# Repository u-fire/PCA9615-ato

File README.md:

# PCA9615

📒 [Datasheet](https://www.nxp.com/docs/en/data-sheet/PCA9615.pdf)

This repository is an [atopile](https://atopile.io/) module for the PCA9615, 2-channel multipoint Fast-mode differential I2C-bus. In other words, it lets
you use I2C like you might use MODBUS, ie. over long wires and through noisy environments. 

## 🏁 Get started
### Installation
From inside a project directory terminal: `ato install PCA9615-ato`

### Code
```ato
from "pca9615/elec/src/pca9615.ato" import PCA9615
from "generics/interfaces.ato" import DiffPair, Power, I2C, GPIO

module Test:
    # define virtual buses, connect these to physical components/pins
    power = new Power
    d_sda = new DiffPair
    d_scl = new DiffPair
    i2c = new I2C
    power_a_2v3_5v5 = new Power
    power_b_3v0_5v5 = new Power
    differential_side_power = new Power
    en = new GPIO

    # define the PCA9615
    pca9615 = new PCA9615

    # PCA9615 enable pin is driven high be an internal pullup
    # to disable chip, drive low
    en ~ pca9615.en

    # connect power to normal I2C side
    power_a_2v3_5v5 ~ pca9615.power_a_2v3_5v5

    # differential power can be seperate or the same as the I2C side
    pca9615.power_b_3v0_5v5 ~ power_a_2v3_5v5
    # - or -
    pca9615.power_b_3v0_5v5 ~ differential_side_power

    # normal I2C connection
    i2c ~ pca9615.i2c

    # differential pairs
    d_sda ~ pca9615.d_sda
    d_scl ~ pca9615.d_scl
```

## 🤔 Design Considerations
- d_sda and d_scl must be routed as differential pairs (`6` in KiCAD PCB Editor)
- power on the I2C side can be separate from the differential side, common grounds are not required
- the I2C side can accept between 2.3 - 5.5 volts
- the differential side can accept 3.0 - 5.5 volts
- an RJ45 connector and CAT6 cable work well for making the connections

## 🔌 Connections

|MCU        |       | MCU PCA9615   |       |Sensor PCA9615     | | Sensor |
|-------:   |-:    |---:                  |:-:         |:---           |:-: | :-|
|  |      | MCU PCA9615.d_SDA 🟩|~            |🟩 PCA9615.d_SDA|~ | 
| |      | MCU PCA9615.d_SCL 🟪|~            |🟪 PCA9615.d_SCL|~
| MCU.SDA 🟨 |~      | 🟨 PCA9615.SDA 🟨|            |🟨 PCA9615.SDA|~ |🟨 Sensor.SDA
| MCU.SCL 🟦 |~      | 🟦 PCA9615.SCL 🟦|            |🟦 PCA9615.SCL|~ |🟦 Sensor.SCL
| *MCU.VCC* 🟥      | ~| 🟥 *PCA9615.VCC* 🟥 |*(optional)*|🟥 *PCA9615.VCC*|~ | 🟥 *Sensor.VCC*
|**MCU.GND**⬛      |~       | ⬛ **PCA9615.GND** ⬛|*(optional)*|⬛ **PCA9615.GND**|~|⬛ **Sensor.GND**

## ⚡ Programming
Once connected, the sensor (or just the other side) appear as a normal I2C device to the host. Nothing special needs to be done.

## 🙏 Contributing
This design is intended to be a community best-effort at a minimal circuit combining:
- datasheet reference design
- readily available components
- modular and reusable layout

You are greatly encouraged to contribute or discuss any improvements here so that everyone may benefit. 

## License
[CERN-OHL-P v2](https:/cern.ch/cern-ohl)

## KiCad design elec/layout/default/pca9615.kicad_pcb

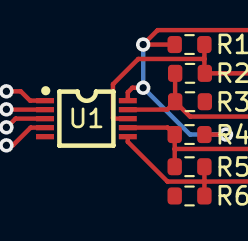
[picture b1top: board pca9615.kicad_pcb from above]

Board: 2 copper layers, 7 parts (0 on the bottom side), 6 nets.

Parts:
R1, R3, R4, R6: Chip Resistor - Surface Mount 300Ohms ±5% 1/10W 0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; R0603
R2, R5: Chip Resistor - Surface Mount 100Ohms ±5% 1/10W 0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; R0603
U1: TSSOP-10_L3.0-W3.0-P0.50-LS4.9-BL

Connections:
dsclm: R5.2, R6.1, U1.6
dsclp: R4.2, R5.1, U1.7
dsdam: R2.2, R3.1, U1.9
dsdap: R1.2, R2.1, U1.8
gnd: R3.2, R6.2, U1.5
vdd_b_: R1.1, R4.1, U1.10

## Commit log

2024-03-01 initial publish
2024-03-01 rename and typos
